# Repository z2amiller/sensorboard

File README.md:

# sensorboard
Sensor board using ESP8266
==========================

This is a simple sensor board using an ESP8266.

It is designed to run from 6 volts, or 4xAA batteries.  The software uses the
deep sleep functions of the ESP8266 for power savings, and applies power to the
sensors only when the ESP8266 is powered on.  It posts the sensor data to a 
[prometheus](http://prometheus.io/) [pushgateway](https://github.com/prometheus/pushgateway).
A copy of this sensor has run for more than two months on 4xAA batteries.
Longer life can be achieved by using a longer sleep interval; the ESP8266
consumes quite a bit of power at bootup and when communicating over wifi.

Hardware:
---------

* [ESP8266](https://github.com/esp8266/Arduino) is a fully featured wifi
  module with embedded microcontroller.  This project can make use of the
  [ESP-07](http://www.banggood.com/ESP8266-ESP-07-Remote-Serial-Port-WIFI-Transceiver-Wireless-Module-p-961247.html)
  module or any of the
  [ESP-12](http://www.banggood.com/ESP8266-ESP-12E-Remote-Serial-Port-WIFI-Transceiver-Wireless-Module-p-980984.html)
  variants - the extra pins at the bottom are unused.  If using the ESP-07
  with the always-on status LED, you may want to desolder / pry off the
  status LED to extend your battery life.
* [DHT22](http://www.electrodragon.com/product/dht22-pre-order-link/) is a
  temperature and humidity sensor.  It is actually the most expensive part
  of this board, even more expensive than the ESP8266.
* [BMP180](http://www.banggood.com/BMP180-Digital-Barometric-Pressure-Sensor-Module-Board-p-930690.html)
  is a barometric pressure and altitude sensor.
* [LMR16006YDDCR](http://www.ti.com/lit/ds/symlink/lmr16006.pdf) is a 600ma
  adjustable voltage switching power regulator.  While much more expensive
  than the LDO, batteries will last ~twice as long.
* [NR4018T100M](http://www.yuden.co.jp/productdata/catalog/en/wound04_e.pdf)
  is the 10uh inductor used as L1.
* [BME280](http://www.mouser.com/ds/2/783/BST-BME280_DS001-11-844833.pdf) is
  an integrated pressure, humidity, and temperature sensor.  Replaces the
  DHT22 and BMP180 in version 4.0.
* Onboard voltage meter to track the battery voltage.  R4 and R5 make up
  the voltage divider so should be 1% or better tolerance that are
  fairly stable with temperature. 
* Everything else on the board is simple and common.
* This board is intended to be hand-solderable. The smallest components are
  0603 and are marked with hand-soldering pads.

Software:
---------

* This is programmed in the Arduino environment.  It includes some standard
  Adafruit libraries (for DHT22 and BMP085).  The newer "unified" sensor
  libraries don't work with the ESP8266 yet, but the older ones work well.
* This sensorboard posts the data to a prometheus gateway for easy graphing
  and alerting.  The code to get the sensor values is pretty straightforward
  and could be pretty easily adapted to other monitoring systems such as
  Thingspeak or MQTT.
* The [prometheus libraries](https://github.com/z2amiller/libraries/tree/master/prometheus)
  libraries are available in my [libraries](https://github.com/z2amiller/libraries)
  repository. The required i2c library is there as well.

Programming:
------------

* The sensorboard has a 6 pin programming header, and included in this
  repository is a sensorboard\_programmer module intended to be connected to
  this programming header. 
* The sensorboard programmer pulls out the reset and programming pins.  To
  flash a new software version, connect the programmer and press and hold
  the 'PROG' button while hitting reset.  This will reboot the ESP8266 into
  flash mode.
* The sensorboard is designed to use this
  [CP2102 board](http://www.banggood.com/5Pcs-CJMCU-CP2102-USB-To-TTLSerial-Module-UART-STC-Downloader-p-980102.html)
  for the USB interface, and
  [these](http://www.banggood.com/100pcs-Mini-Micro-Momentary-Tactile-Tact-Switch-Push-Button-DIP-P4-p-917570.html)
  cheap tactile switches.  That USB module solders right into the programmer
  board but you could also wire up any USB breakout that supports 3.3 volts.
* Unfortunately the configuration is part of the code.  You'll have to change
  some of the constants in the code to use your wifi SSID/password,
  prometheus pushgateway, etc.

Versions:
---------

Check out the following branches for these released versions:

* [sensorboard-4.0](https://github.com/z2amiller/sensorboard/tree/sensorboard-4.0)
  [oshpark](https://oshpark.com/shared_projects/D1xuf056) UNTESTED:
  Replace the DHT22 and BMP180 with a BME280.  No longer hand-solderable,
  needs a hot air station for the FGA-8 footprint BME280.
* [sensorboard-3.1](https://github.com/z2amiller/sensorboard/tree/sensorboard-3.1)
  [oshpark](https://oshpark.com/shared_projects/4DUu3wyO) TESTED:
  Sensorboard with a switching power supply. Higher parts cost but ~1.6x
  battery life.
* [sensorboard-2.2](https://github.com/z2amiller/sensorboard/tree/sensorboard-2.2)
  [oshpark](https://oshpark.com/shared_projects/rGc3bDv8) TESTED:
  Sensorboard using a LDO for simple build and lower parts cost.

More Links:
-----------

* Order the [sensorboard programmer](https://oshpark.com/shared_projects/fjlzVR1e)
  on OSHPark!
* Check out the [ESP8266 commmunity](http://reddit.com/r/ESP8266) on Reddit!

TODO(z2amiller):
---------------

* Add a picture of the sensorboard in action.
* Add some screenshots of Prometheus graphs.
* Create a prometheus setup tutuorial.
* Create a prometheus dashboard for the ESP8266 sensor data.
* Finish up the code for sensorboard-4.0 with the BME280 sensor.
* Create a sensorboard programmer with a regulator to power the ESP8266
  through the 3v3 pin while programming.

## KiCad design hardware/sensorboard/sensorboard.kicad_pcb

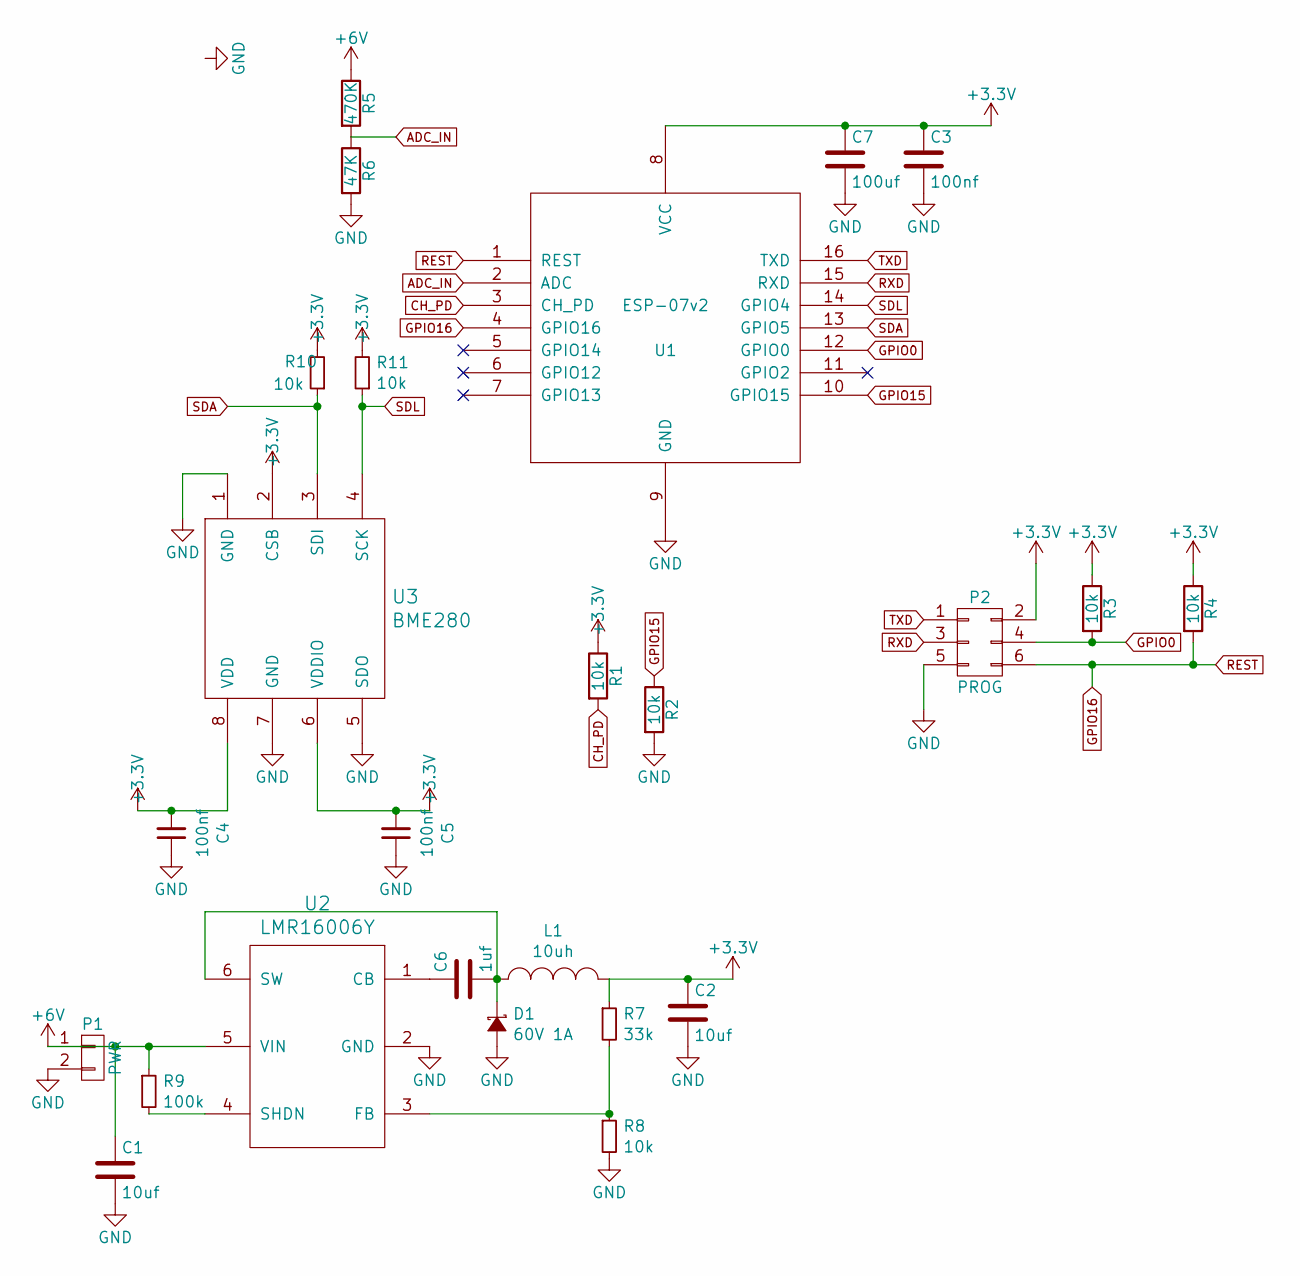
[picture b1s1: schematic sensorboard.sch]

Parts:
C1, C2: 10uf; C_0805_HandSoldering
C3, C4, C5: 100nf; C_0603_HandSoldering
C6: 1uf; C_0603_HandSoldering
C7: 100uf; TantalC_SizeD_EIA-7343_HandSoldering
D1: 60V 1A; SOD-123
L1: 10uh; NR8040_HandSoldering
P1: PWR; Pin_Header_Straight_1x02
P2: PROG; Pin_Header_Straight_2x03
R1, R2, R3, R4, R8, R10, R11: 10k; R_0603_HandSoldering
R5: 470K; R_0603_HandSoldering
R6: 47K; R_0603_HandSoldering
R7: 33k; R_0603_HandSoldering
R9: 100k; R_0603_HandSoldering
U1: ESP-07v2; ESP-12
U2: LMR16006Y; SOT-23-6
U3: BME280; FGA8

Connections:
+3V3: C2.1, C3.1, C4.2, C5.2, C7.1, L1.2, P2.2, R1.1, R3.1, R4.1, R7.1, R10.2, R11.2, U1.8 (VCC), U3.2 (CSB), U3.6 (VDDIO), U3.8 (VDD)
+6V: C1.1, P1.1, R5.1, R9.1, U2.5 (VIN)
ADC_IN: R5.2, R6.1, U1.2 (ADC)
CH_PD: R1.2, U1.3 (CH_PD)
GND: C1.2, C2.2, C3.2, C4.1, C5.1, C7.2, D1.2 (A), P1.2, P2.5, R2.2, R6.2, R8.2, U1.9 (GND), U2.2 (GND), U3.1 (GND), U3.5 (SDO), U3.7 (GND)
GPIO0: P2.4, R3.2, U1.12 (GPIO0)
GPIO15: R2.1, U1.10 (GPIO15)
GPIO16: P2.6, R4.2, U1.1 (REST), U1.4 (GPIO16)
unnamed: C6.1, U2.1 (CB)
unnamed: C6.2, D1.1 (K), L1.1, U2.6 (SW)
unnamed: R7.2, R8.1, U2.3 (FB)
unnamed: R9.2, U2.4 (SHDN)
RXD: P2.3, U1.15 (RXD)
SDA: R10.1, U1.13 (GPIO5), U3.3 (SDI)
SDL: R11.1, U1.14 (GPIO4), U3.4 (SCK)
TXD: P2.1, U1.16 (TXD)

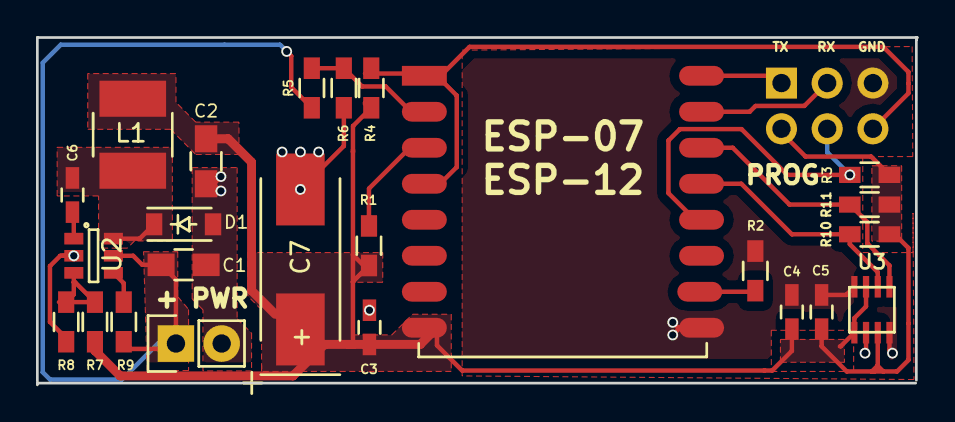
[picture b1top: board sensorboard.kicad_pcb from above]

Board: 2 copper layers, 48.9 x 19.3 mm, 25 parts (1 on the bottom side), 16 nets.

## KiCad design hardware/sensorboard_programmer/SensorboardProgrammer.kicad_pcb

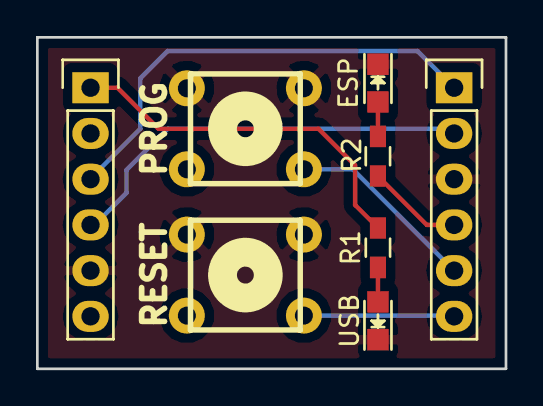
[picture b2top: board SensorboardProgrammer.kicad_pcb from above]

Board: 2 copper layers, 26.0 x 18.4 mm, 8 parts (0 on the bottom side), 9 nets.

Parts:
ESP: ESP; LED-0805
P2: CONN_01X06; Pin_Header_Straight_1x06
PROG: SW_PUSH; PCB_PUSH
R1, R2: 100 ohm; R_0603_HandSoldering
RESET: SW_PUSH; PCB_PUSH
USB: USB; LED-0805
USB MODULE: CONN_01X06; Pin_Header_Straight_1x06

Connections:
GND: ESP.1, P2.3, PROG.2, PROG.4, RESET.2, RESET.4, USB.1, USB MODULE.5
unnamed: R1.1, USB.2
unnamed: ESP.2, R2.1
unnamed: R1.2, USB MODULE.1
unnamed: P2.4, R2.2
unnamed: P2.5, PROG.3
unnamed: P2.6, RESET.3
RXI: P2.1, USB MODULE.3
TXO: P2.2, USB MODULE.4

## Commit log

2015-10-17 Move sensorboard stuff to dedicated repository.
2015-10-17 Formatting fixes.
2015-10-24 Change footprint of power connector, move ino file
2015-10-25 Read voltage from A0 instead of internal VCC.
2015-10-25 Measure the actual battery voltage on ADC pin.
2015-10-25 Remove backup file.
2015-10-25 Fix scaling factor of ADC.
2015-10-31 Change some footprints.
2015-10-31 Change some footprints from 0805 to 0603.
2015-10-31 Backup.
2015-11-04 Better silkscreening and status LEDs.
2015-11-04 A few more silkscreen changes.
2015-11-04 Add LEDs and improved silkscreens.
2015-11-05 Add MIT license for sensorboard hardware and code.
2015-11-05 Add real documentation for the sensorboard project.
2015-11-08 Changed power connector, improved silkscreen.
2015-11-08 Improved silkscreening for sensorboard.
2015-11-08 Change URL for oshpark project.
2015-11-21 Change bmp180 label visibility.
2015-11-21 Fix silkscreen error - PRG and 3v3 were reversed..
2016-02-27 Attempt one at switching power supply.
2016-02-28 Fix up silkscreening
2016-02-28 Fix up the bottom edge cuts
2016-02-28 Bro do you even switch
2016-02-28 Fix up the 3v3 traces
2016-02-28 Some silkscreen cleanup
2016-03-05 Use smaller inductor, shrink board a little
2016-03-05 Fix some silkscreens
2016-03-05 Better routing of 3v3
2016-03-05 Remove extra 3v3 via, add better ground connection
2016-03-05 Fix up readme with version information.
2016-04-03 Refactor to use prometheus lib and timers.
2016-04-03 Improve initial connection time.
2016-04-04 Use bme280 for sensor - initial commit
2016-04-04 Fix sensor placement and improve silkscreens
2016-04-04 Fixed soldermask around the bme280
2016-04-05 Don't disconnect WiFi.
2016-04-26 Add a file talking about low power ESP8266.
2016-04-26 Fixed some silkscreens, added BOM.
2016-04-27 Fix code formatting.
2016-04-27 Code formatting, take two.
2016-04-27 Documentation fixes.
2016-04-27 Some more documentation cleanup.
2016-04-27 Added some more TODOs, work is never done.
2016-04-27 Now with more math
2016-04-28 Some more documentation cleanups.
2016-04-30 Code for sensorboard 4.0 using adafruit bme280 lib.
2016-04-30 Add some comments to configuration parameters.
2016-06-18 More regulator examples, talk about NodeMCU.
2016-06-18 A few more documentation cleanups.
2016-09-13 Update library documentation.
